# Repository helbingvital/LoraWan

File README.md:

# LoRaWAN Seminar Project

Welcome to the **LoRaWAN Seminar Project** repository! This project focuses on interfacing a DS18B20 temperature sensor with a LoRaWAN network, using a Dragino gateway for data transmission and visualization on The Things Network (TTN) dashboard.

## Repository Overview

This repository contains the following resources:

### Source Code
- **`main.c`**: Main application file for hardware initialization and LoRaWAN communication.
- **`LoraWAN2.h`**: Header file with utilities and definitions for LoRaWAN functions.
- **`HAL_MSP430.c`** / **`HAL_MSP430.h`**: Hardware Abstraction Layer. Pin configuration used in this setup and hardware specific funtionalities.
- **`ds18b20.c`** / **`ds18b20.h`**: Source and header files for interacting with the DS18B20 temperature sensor.
- **`payloaddecoder.js`**: Uplink Payload decoder used in TTN.

### Hardware
- **`hardware/LoraWAN_Platine_board.brd`**: PCB layout for the custom LoRaWAN hardware.
- **`hardware/LoraWAN_Platine_schematic.sch`**: Circuit schematic for hardware assembly.
- **`hardware/3D Case MSP430 LoraWAN V2.f3d`**: Fusion file containing the design of the custom case for 3D printing.

## Prerequisites

To build and run this project, ensure you have the following:

### Software
- **Development Environment**: [Code Composer Studio Theia](https://www.ti.com/tool/CODECOMPOSER).

### Hardware Components
- **Development Board**: MSP430G2ET development kit (uses a MSP430G2553 microcontroller).
- **LoRaWAN Module**: Seeed Studio Wio-E5-LE-HF, mounted on a custom PCB (files in the `hardware` directory).
- **Temperature Sensor**: DS18B20, connected to the MSP430.
- **LoRaWAN Gateway**: Dragino LPS8N.
- **Case**: 3D printable Case.

## Getting Started

### 1. Hardware Setup

1. Assemble the hardware using the provided PCB layout (**`LoraWAN_Platine_board.brd`**) and schematic (**`LoraWAN_Platine_schematic.sch`**).
2. Connect the DS18B20 temperature sensor and the Wio-E5 module as specified in the schematic.
3. Attach the custom PCB to the MSP430G2553 development kit.
4. Set up the Dragino LPS8N gateway:
   - Connect the gateway to the Internet.
   - Follow the [Dragino LPS8N User Manual](https://www.dragino.com/downloads/downloads/LoRa_Gateway/LPS8/LPS8_LoRaWAN_Gateway_User_Manual_v1.3.2.pdf) for configuration.
5. Print the top and button part of the Case in **`3D Case MSP430 LoraWAN V2.f3d`** and place the MSP430 board including the custom PCB in it.

### 2. Software Setup

1. Open the project in **Code Composer Studio Theia**.
2. Hardware set up in **'HAL_MSP430.h'**: Update Pin Configuration for UART, Sensor Data, Button, and LED. Set User.
3. Configure the LoRaWAN credentials:
   - Retrieve the DevID and other parameters for your Wio-E5 module using AT commands. To do so, set #define SETUP_MODE 1 in 'main.c'. Also set the AppKey.
   - Register the device and configure the IDs in your TTN dashboard. Change the AppKey in 'LoraWan2.c'.
   - Refer to the [Wio-E5 Module Documentation](https://wiki.seeedstudio.com/LoRa-E5_STM32WLE5JC_Module/) for details.
5. Confirm that the message identifiers used match the decoder on TTN. ('LoraWan2.h')
   - If not change your device's uplink payload formatter in the TTN to the one in **`payloaddecoder.js`**.
6. Compile the project.
7. Flash the compiled code to the MSP430 microcontroller.

### 3. Running the Application

1. Power on the hardware.
2. The application will:
   - Initialize the hardware.
   - Read temperature data from the DS18B20 sensor.
   - Transmit the temperature data via LoRaWAN at regular intervals.
3. View the transmitted data in real-time on the TTN live data console.

## Contribution

This project was developed as part of a seminar at [**MedIT, RWTH Aachen University**](https://www.medit.hia.rwth-aachen.de/) under supervision of **Marian Walter**, by **Celina Helbing Vital** and **Oliver Schirrmacher**.

## Contact

For any questions or support, please contact the project maintainers at [**MedIT, RWTH Aachen University**](https://www.medit.hia.rwth-aachen.de/).

## Copyright
If code from other sources has been used, the respective copyright notices are included directly in the code files.
The file **`hardware/3D Case MSP430 LoraWAN V2.f3d`** was created using a modified version of the template from [Thingiverse](https://www.thingiverse.com/thing:4651831). The original design was made by **JOHNeMac36** and is licensed under the **GNU General Public License (GPL)**.

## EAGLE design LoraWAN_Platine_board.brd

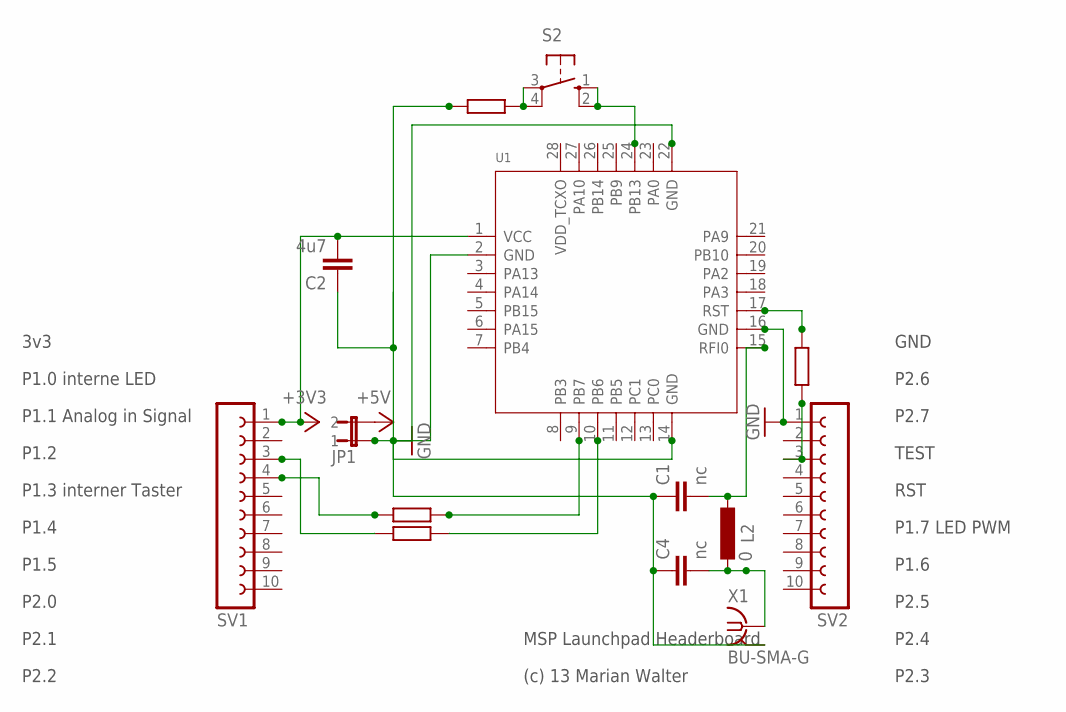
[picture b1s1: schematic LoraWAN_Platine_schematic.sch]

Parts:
C1, C4: nc; C0805
C2: 4u7; C1206
JP1: JP1E; JP1
L2: 0; L1812
R1, R2, R3: 22; 0204/7
R4: 1k; 0204/7
S2: 10-XX; B3F-10XX
SV1, SV2: FE10-1; FE10
U1: MODULE_LORA_E5; MODULE28P-1.25-12X12X2.5MM
X1: BU-SMA-G

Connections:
+3V3: C2.2, SV1.1, U1.1 (VCC)
+5V: JP1.2
GND: C1.1, C2.1, C4.1, JP1.1, R4.1, SV2.1, U1.2 (GND), U1.14 (GND), U1.16 (GND), U1.22 (GND), X1.2, X1.3 (2), X1.4 (2), X1.5 (2)
unnamed: C1.2, L2.1, U1.15 (RFI0)
unnamed: R2.2, U1.9 (PB7)
unnamed: R2.1, SV1.4
unnamed: R1.2, U1.10 (PB6)
unnamed: R1.1, SV1.3
unnamed: R3.2, U1.17 (RST)
unnamed: R3.1, SV2.3
unnamed: C4.2, L2.2, X1.1
unnamed: R4.2, S2.3, S2.4 (P1)
unnamed: S2.1 (S), S2.2 (S1), U1.24 (PB13)

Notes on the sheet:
P1.0 interne LED
P1.1 Analog in Signal
P1.2
P1.3 interner Taster
3v3
P1.4
P2.0
P2.1
P2.2
GND
P2.6
P2.7
TEST
RST
P1.7 LED PWM
P1.6
P2.5
P2.4
P2.3
P1.5
MSP Launchpad Headerboard
(c) 13 Marian Walter

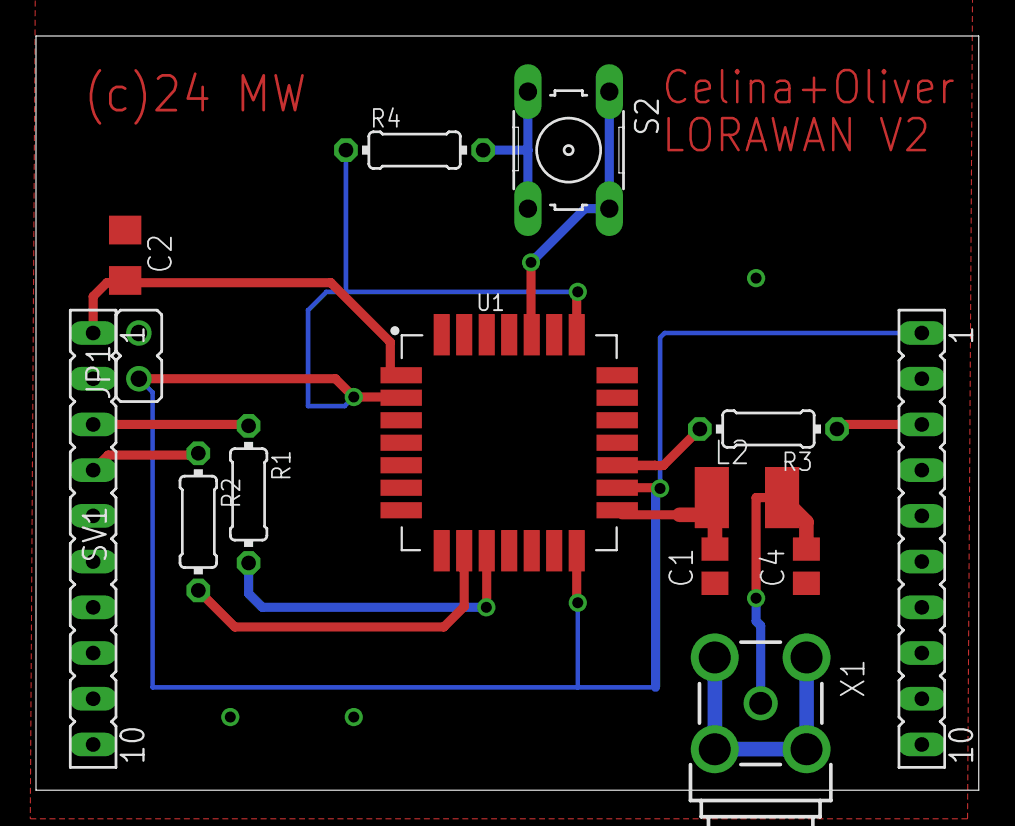
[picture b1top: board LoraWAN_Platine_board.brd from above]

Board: 2 copper layers, 52.4 x 41.9 mm, 18 parts (0 on the bottom side), 12 nets.

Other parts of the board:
U$2, U$3, U$4, U$5: PASSMARK

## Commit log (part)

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2024-12-10 Initial commit.
2024-12-10 Get Temperature
2024-12-10 Unterscheiden zwischen beiden Module
    Unterscheiden zwischen beiden Module
2024-12-10 Temperature Sensor Power and Conversion.
2024-12-17 Add hardware files
2024-12-17 Create t
2024-12-17 Comments. Unify Macros used for Temperature Sensor
2024-12-17 Creation of LoraWan.c, clean up.
2025-01-07 Identifier Status Messages. Error Identifier for Data msg explained.
2025-01-07 Fix Data Message as MSG_HEX.
2025-01-07 Code Cleanup and Documentation.
2025-01-14 Code Clean up. Hardware abstraction
2025-01-21 Hardware Abstraction Layer
2025-01-23 Old version without button
2025-01-25 Replace DELAY with timer module to ensure interrupt functionalities.
2025-01-26 Add Case Design file
2025-01-26 Update README.md
    Update README.md
2025-01-27 Action on Button press.
2025-01-28 Wait for MSG: Done reply.
2025-01-28 Fix modem busy when button press
2025-01-28 Retry JOIN if unseccessful.
2025-01-28 JOIN if message fails due to disconnect.
